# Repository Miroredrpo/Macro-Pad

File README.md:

#  MacroPad

**MacroPad** is a 4by4 keyboard which uses hotswappable mechanical switches and uses a micro-controller
so that it can be used a stream deck as well as the indivisual keys are programmable manually in the firmware 
folder
---

##  Overview

**MacroPad** is a 4by4 keyboard which uses hotswappable mechanical switches and uses a micro-controller
so that it can be used a stream deck as well as the indivisual keys are programmable manually in the firmware 
folder 

## PCB design :

this pcb design is the design layout ony for the hot swapable keys and the rest of the conponents can be placed at the bottom of the pcb here :

## PCB front side :

this is the pcb in 3d view and the components can be seen placed in there respective places, there are places to put in indivisual 
led aswell to make the macro pad backlit as well 

## PCB backside :

## 3d Case :

this is the 3d case that will be used to hold the pcb in place, then have a connecter comeout fom the hole made.

---

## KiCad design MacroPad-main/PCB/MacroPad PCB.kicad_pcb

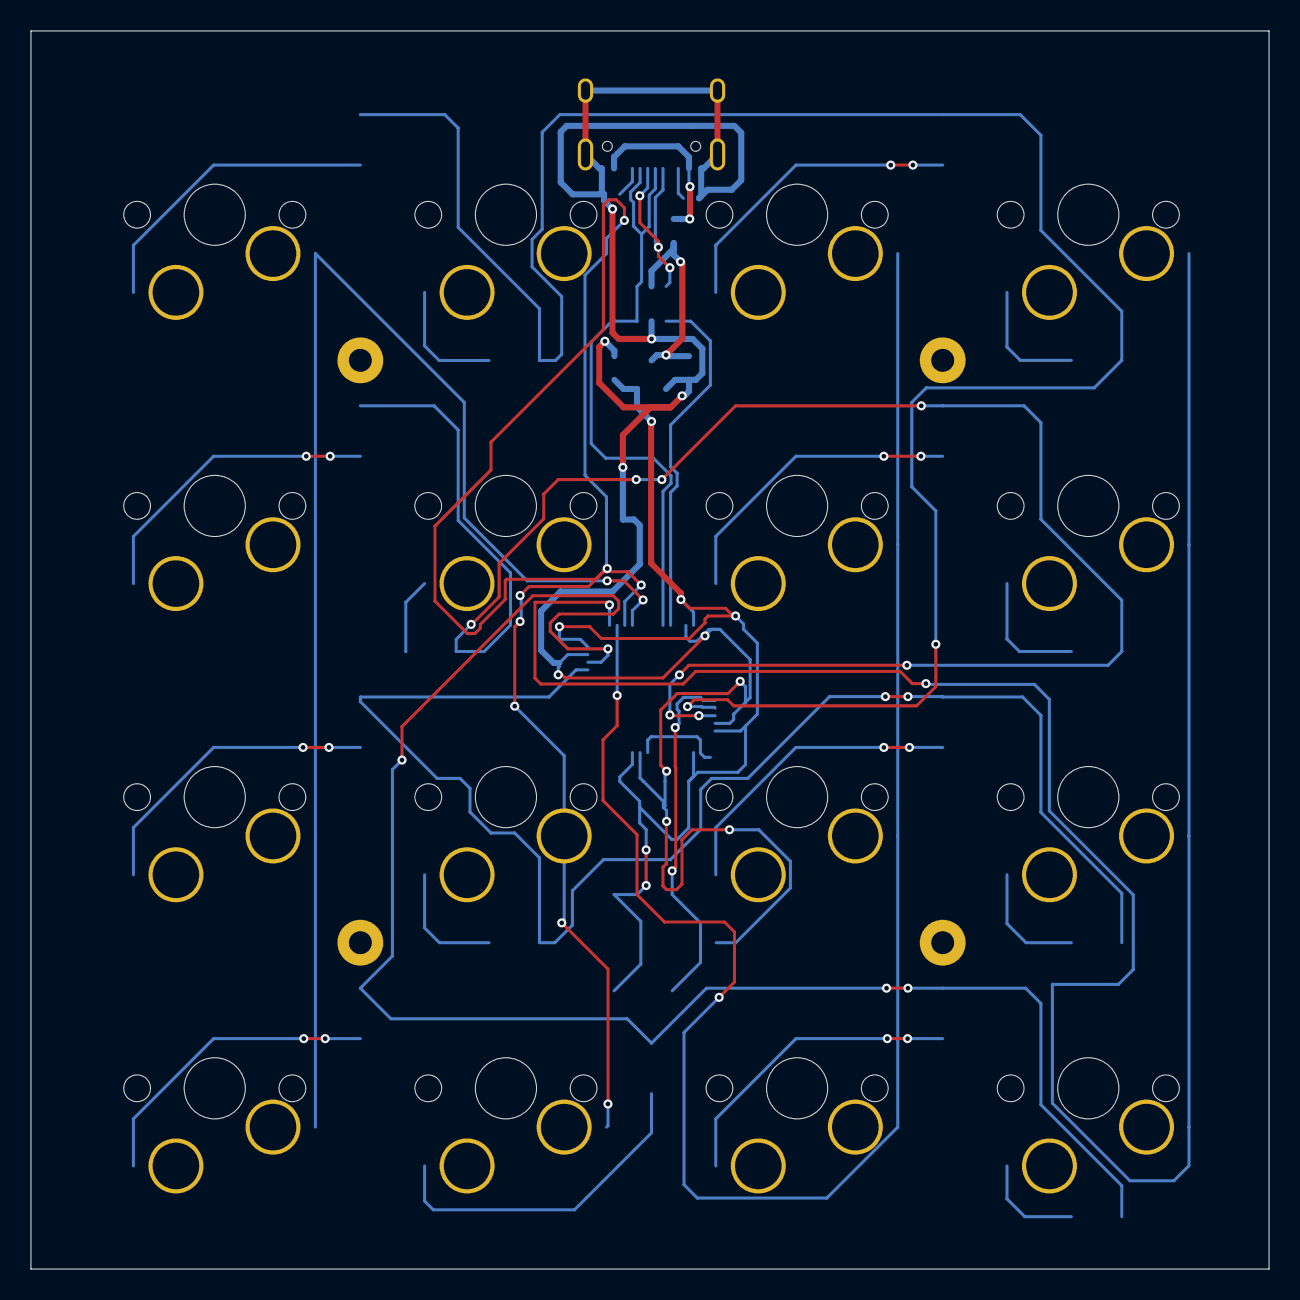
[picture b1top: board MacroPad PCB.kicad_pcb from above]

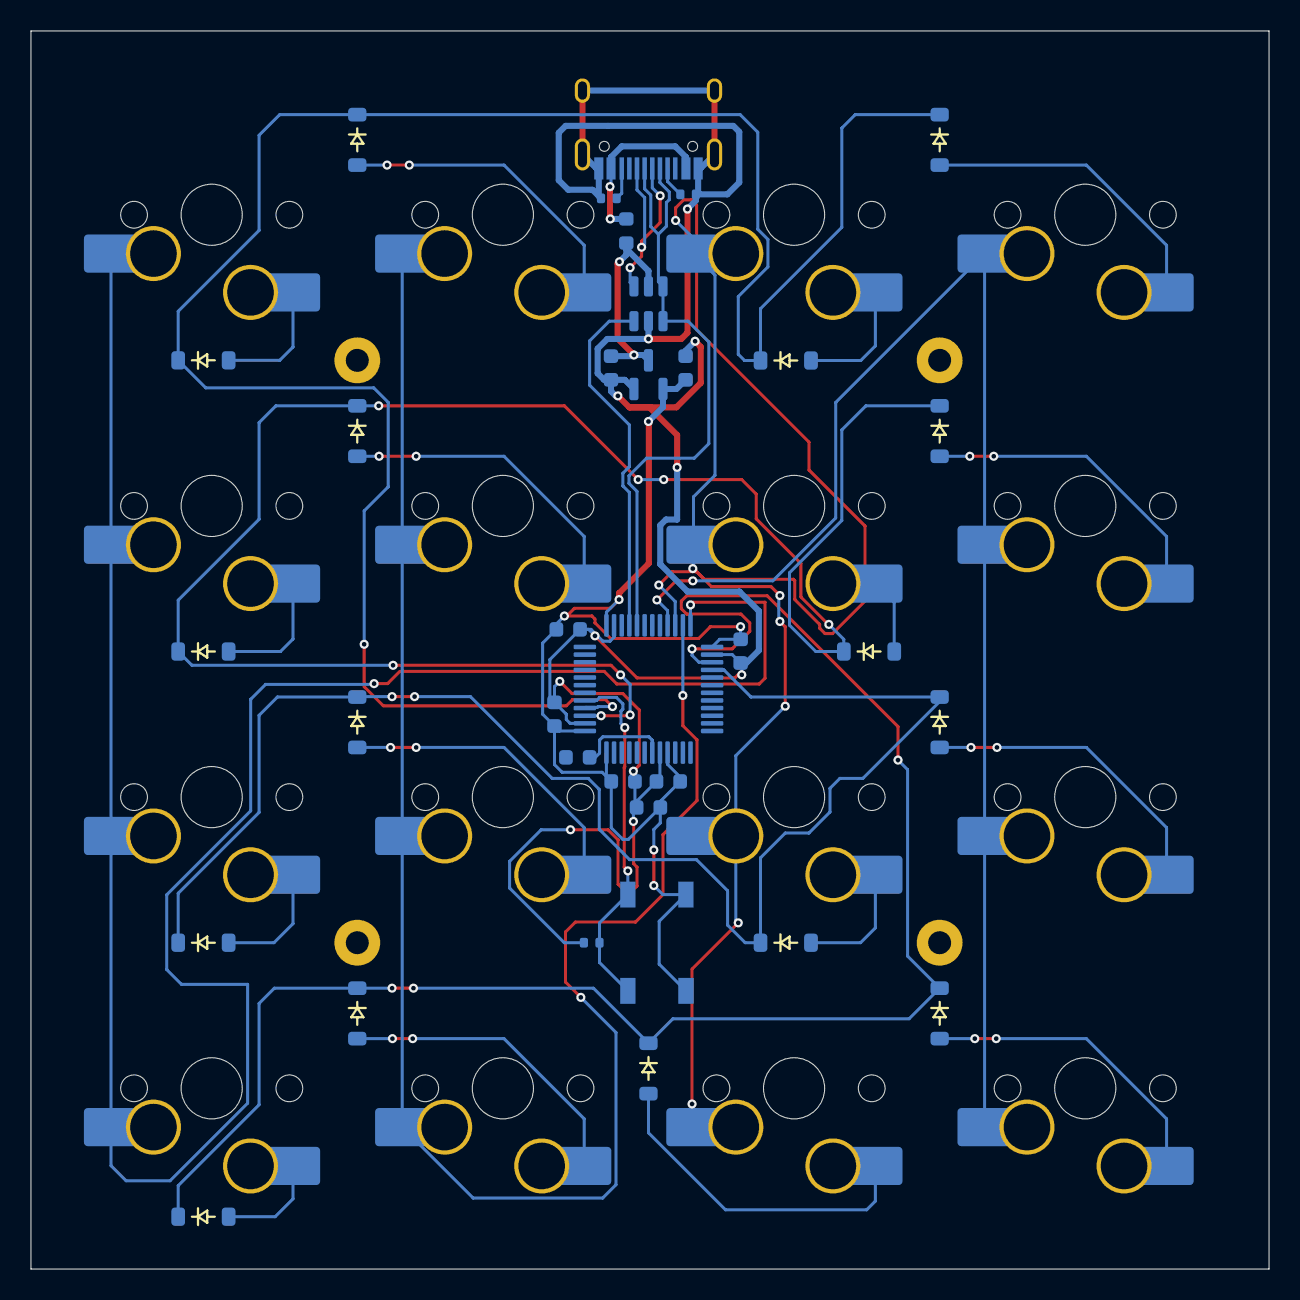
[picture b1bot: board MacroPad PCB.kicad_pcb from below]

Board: 2 copper layers, 81.0 x 81.0 mm, 50 parts (50 on the bottom side), 34 nets.

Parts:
C1, C2, C3, C4, C5, C6: 100nf; Capacitor_0603
C7: 10uf; Capacitor_0603
C8, C9: 1uf; Capacitor_0603
D1, D2, D3, D4, D5, D6, D7, D8, D9, D10, D11, D12, D13, D14, D15, D16: Diode; Diode_SOD-123
F1: 500mA; Fuse_0603
J1: USB_C_Receptacle_USB2.0_14P; USB_C_HRO_TYPE-C-31-M-12
R1: 10K; Resistor_0402
R2, R3: 5.1K; Resistor_0402
S1, S2, S3, S4, S5, S6, S7, S8, S9, S10, S11, S12, S13, S14, S15, S16: Keyswitch; MX_Hotswap_1.00u
SW1: SW_Push; Button_TL3342
U1: STM32F103C8Tx; Package_LQFP-48_7x7mm_P0.5
U2: USBLC6-2P6; ESD_SOT-23-6
U3: XC6206PxxxMR; Voltage_SOT-23

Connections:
+3V3: C2.1, C3.1, C4.1, C5.1, C6.1, C7.1, C9.1, SW1.1, U1.1 (VBAT), U1.9 (VDDA), U1.24 (VDD), U1.36 (VDD), U1.48 (VDD), U3.2 (VO)
+5V: C8.1, F1.2, U2.5 (VBUS), U3.3 (VI)
BOOT0: R1.1, SW1.2, U1.44 (BOOT0)
Column 1: S1.1, S5.1, S9.1, S13.1, U1.28 (PB15)
Column 2: S2.1, S6.1, S10.1, S14.1, U1.27 (PB14)
Column 3: S3.1, S7.1, S11.1, S15.1, U1.26 (PB13)
Column 4: S4.1, S8.1, S12.1, S16.1, U1.25 (PB12)
D+: J1.A6 (D+), J1.B6 (D+), U1.33 (PA12), U2.1 (I/O1), U2.6 (I/O1)
D-: J1.A7 (D-), J1.B7 (D-), U1.32 (PA11), U2.3 (I/O2), U2.4 (I/O2)
GND: C1.1, C2.2, C3.2, C4.2, C5.2, C6.2, C7.2, C8.2, C9.2, J1.A1 (GND), J1.A12 (GND), J1.B1 (GND), J1.B12 (GND), J1.S1 (SHIELD), R1.2, R2.2, R3.2, U1.8 (VSSA), U1.23 (VSS), U1.35 (VSS), U1.47 (VSS), U2.2 (GND), U3.1 (GND)
unnamed: D1.2 (A), S1.2
unnamed: D2.2 (A), S2.2
unnamed: D3.2 (A), S3.2
unnamed: D4.2 (A), S4.2
unnamed: D5.2 (A), S5.2
unnamed: D6.2 (A), S6.2
unnamed: D7.2 (A), S7.2
unnamed: D8.2 (A), S8.2
unnamed: D9.2 (A), S9.2
unnamed: D10.2 (A), S10.2
unnamed: D11.2 (A), S11.2
unnamed: D12.2 (A), S12.2
unnamed: D13.2 (A), S13.2
unnamed: D14.2 (A), S14.2
unnamed: D15.2 (A), S15.2
unnamed: D16.2 (A), S16.2
unnamed: J1.A5 (CC1), R2.1
unnamed: J1.B5 (CC2), R3.1
unnamed: C1.2, U1.7 (NRST)
Row 1: D1.1 (K), D2.1 (K), D3.1 (K), D4.1 (K), U1.22 (PB11)
Row 2: D5.1 (K), D6.1 (K), D7.1 (K), D8.1 (K), U1.21 (PB10)
Row 3: D9.1 (K), D10.1 (K), D11.1 (K), D12.1 (K), U1.46 (PB9)
Row 4: D13.1 (K), D14.1 (K), D15.1 (K), D16.1 (K), U1.45 (PB8)
VBUS: F1.1, J1.A4 (VBUS), J1.A9 (VBUS), J1.B4 (VBUS), J1.B9 (VBUS)

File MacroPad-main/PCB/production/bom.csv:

Designator,Footprint,Quantity,Value,LCSC Part #
"_4, _3, _2, ",,4,,
"C1, C2, C3, C4, C5, C6",Capacitor_0603,6,100nf,
C7,Capacitor_0603,1,10uf,
"C8, C9",Capacitor_0603,2,1uf,
"D1, D10, D11, D12, D13, D14, D15, D16, D2, D3, D4, D5, D6, D7, D8, D9",Diode_SOD-123,16,Diode,
F1,Fuse_0603,1,500mA,
J1,USB_C_HRO_TYPE-C-31-M-12,1,USB_C_Receptacle_USB2.0_14P,
R1,Resistor_0402,1,10K,
"R2, R3",Resistor_0402,2,5.1K,
"S1, S10, S11, S12, S13, S14, S15, S16, S2, S3, S4, S5, S6, S7, S8, S9",MX_Hotswap_1.00u,16,Keyswitch,
SW1,Button_TL3342,1,SW_Push,
U1,Package_LQFP-48_7x7mm_P0.5,1,STM32F103C8Tx,
U2,ESD_SOT-23-6,1,USBLC6-2P6,
U3,Voltage_SOT-23,1,XC6206PxxxMR,

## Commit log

2025-10-27 Initial commit/maybe final commit
2025-10-28 Revise README for clarity and formatting
    Updated README to improve clarity and fix formatting issues.
2025-10-28 Update README with 3D case description
    Added description of the 3D case for PCB.
2025-10-28 Enhance README with PCB and case details
    Added sections for PCB front side, backside, and 3D case in the README.
2025-10-28 Update README with 3D case information
    Added description and image for the 3D case used to hold the PCB.
2025-10-28 Fix spelling errors in README.md
    Corrected spelling errors in the README file.
